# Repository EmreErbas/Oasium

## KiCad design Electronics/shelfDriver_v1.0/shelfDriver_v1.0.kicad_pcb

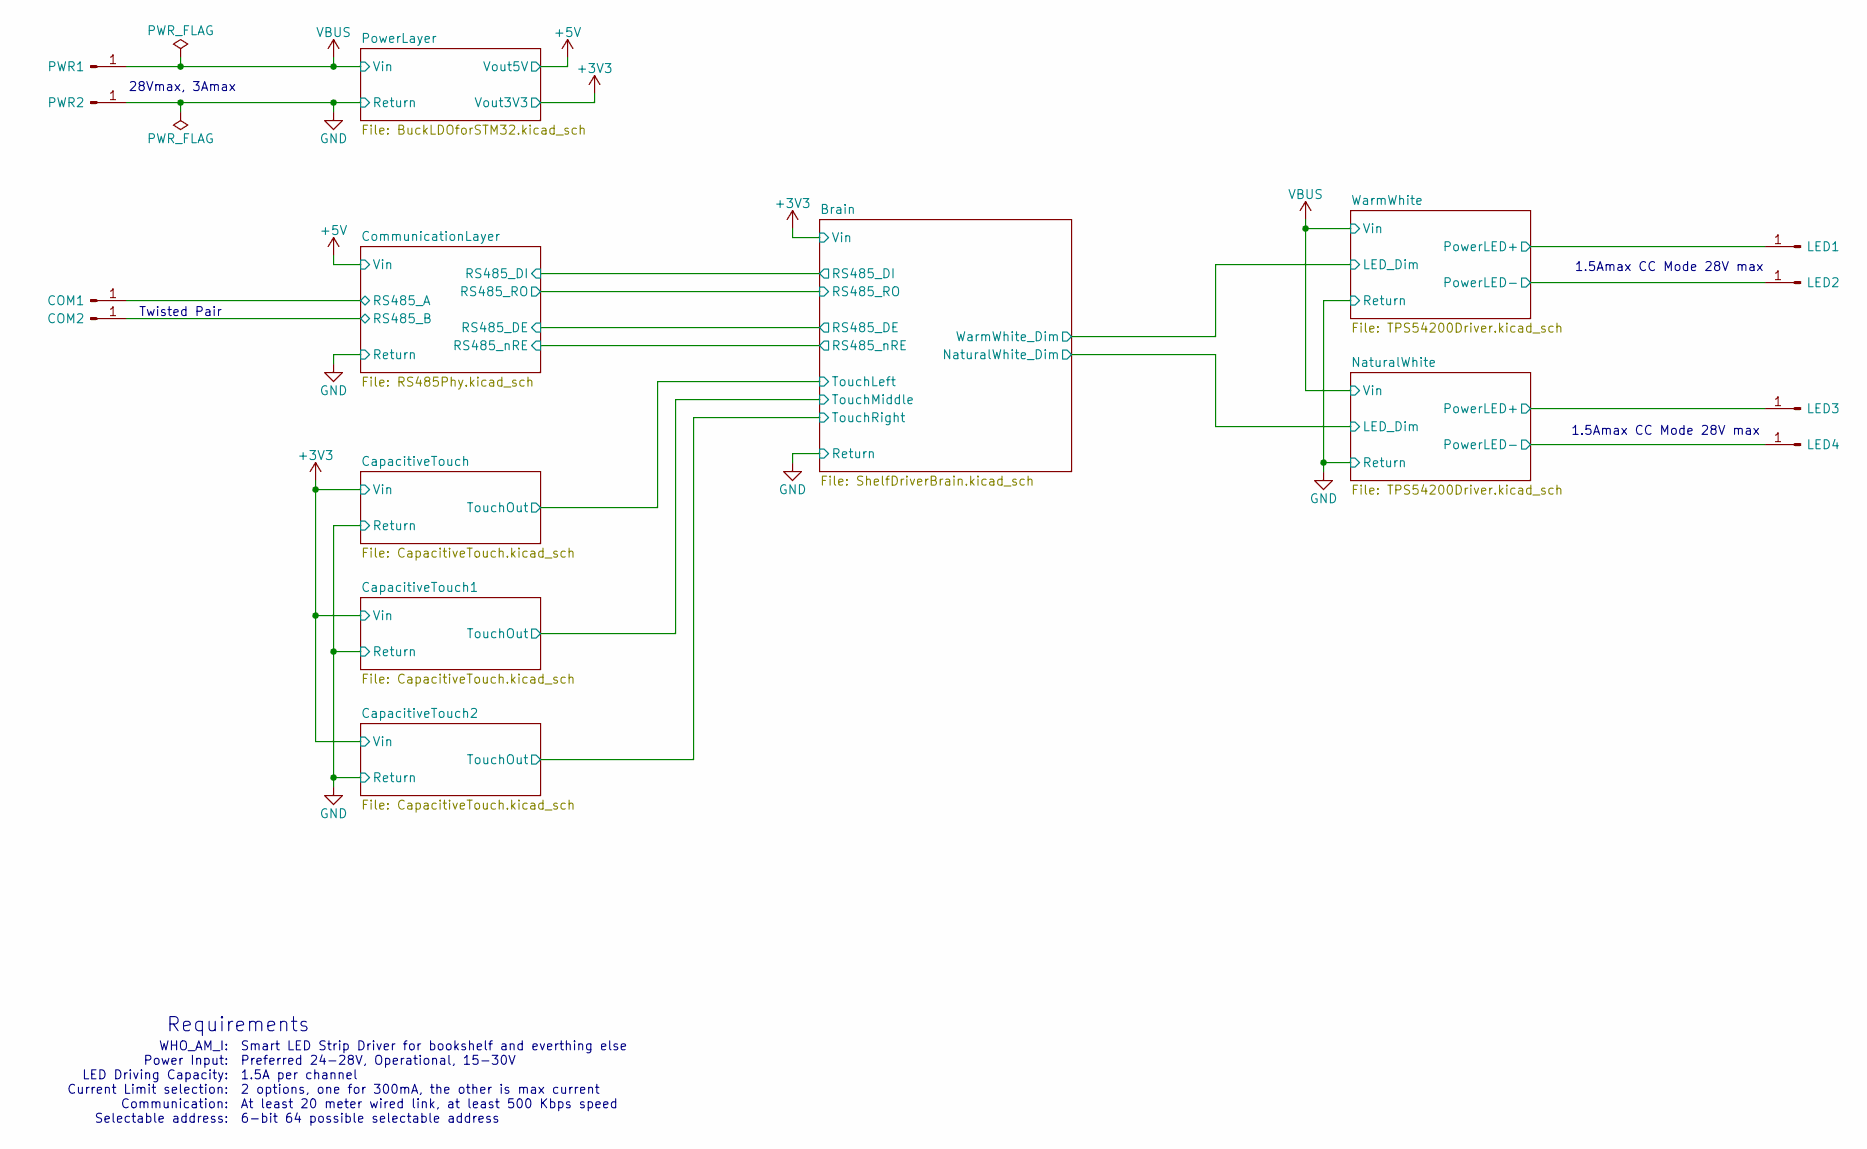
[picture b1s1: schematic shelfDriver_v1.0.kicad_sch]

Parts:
COM1, COM2: Conn_01x01_Pin; SolderPt_2.5x4mm
LED1, LED2, LED3, LED4: Conn_01x01_Pin; SolderPt_2.5x4mm
PWR1, PWR2: Conn_01x01_Pin; SolderPt_2.5x4mm

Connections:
/CommunicationLayer/RS485_A: COM1.1; also elsewhere on the board
/CommunicationLayer/RS485_B: COM2.1; also elsewhere on the board
/NaturalWhite/PowerLED+: LED3.1; also elsewhere on the board
/NaturalWhite/PowerLED-: LED4.1; also elsewhere on the board
/WarmWhite/PowerLED+: LED1.1; also elsewhere on the board
/WarmWhite/PowerLED-: LED2.1; also elsewhere on the board
GND: PWR2.1; also elsewhere on the board
VBUS: PWR1.1; also elsewhere on the board

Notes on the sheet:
Requirements
Smart LED Strip Driver for bookshelf and everthing else Preferred 24-28V, Operational, 15-30V 1.5A per channel 2 options, one for 300mA, the other is max current At least 20 meter wired link, at least 500 Kbps speed 6-bit 64 possible selectable address
1.5Amax CC Mode 28V max
28Vmax, 3Amax
Twisted Pair
WHO_AM_I: Power Input: LED Driving Capacity: Current Limit selection: Communication: Selectable address:

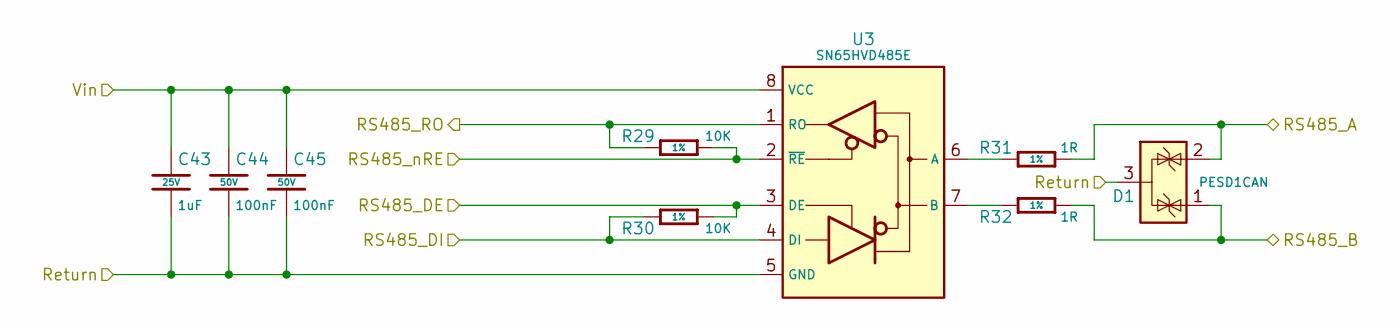
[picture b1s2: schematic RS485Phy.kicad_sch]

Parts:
C43: 1uF; C-0402; Voltage 25V; MFR. Part # CL05A105KA5NQNC; JLCPCB Part # C52923
C44, C45: 100nF; C-0402; Voltage 50V; MFR. Part # CL05B104KB54PNC; JLCPCB Part # C307331
D1: PESD1CAN; SOT-23; MFR. Part # PESD1CAN; JLCPCB Part # C343993
R29, R30: 10K; R-0402; Tolerance 1%; MFR. Part # 0402WGF1002TCE; JLCPCB Part # C25744
R31, R32: 1R; R-0402; Tolerance 1%; MFR. Part # 0402WGF100KTCE; JLCPCB Part # C25086
U3: SN65HVD485E; Texas_R-PDSO-G8; MFR.Part # SN65HVD485EDR; JLCPCB Part # C27899

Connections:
+5V: C43.1, C44.1, C45.1, U3.8 (VCC); also elsewhere on the board
/Brain/RS485_DE: R30.2, U3.3 (DE); also elsewhere on the board
/Brain/RS485_DI: R30.1, U3.4 (DI); also elsewhere on the board
/Brain/RS485_RO: R29.1, U3.1 (RO); also elsewhere on the board
/Brain/RS485_nRE: R29.2, U3.2 (~RE); also elsewhere on the board
/CommunicationLayer/RS485_A: D1.2 (K), R31.2; also elsewhere on the board
/CommunicationLayer/RS485_B: D1.1 (K), R32.2; also elsewhere on the board
GND: C43.2, C44.2, C45.2, D1.3 (A), U3.5 (GND); also elsewhere on the board
unnamed: R31.1, U3.6 (A)
unnamed: R32.1, U3.7 (B)

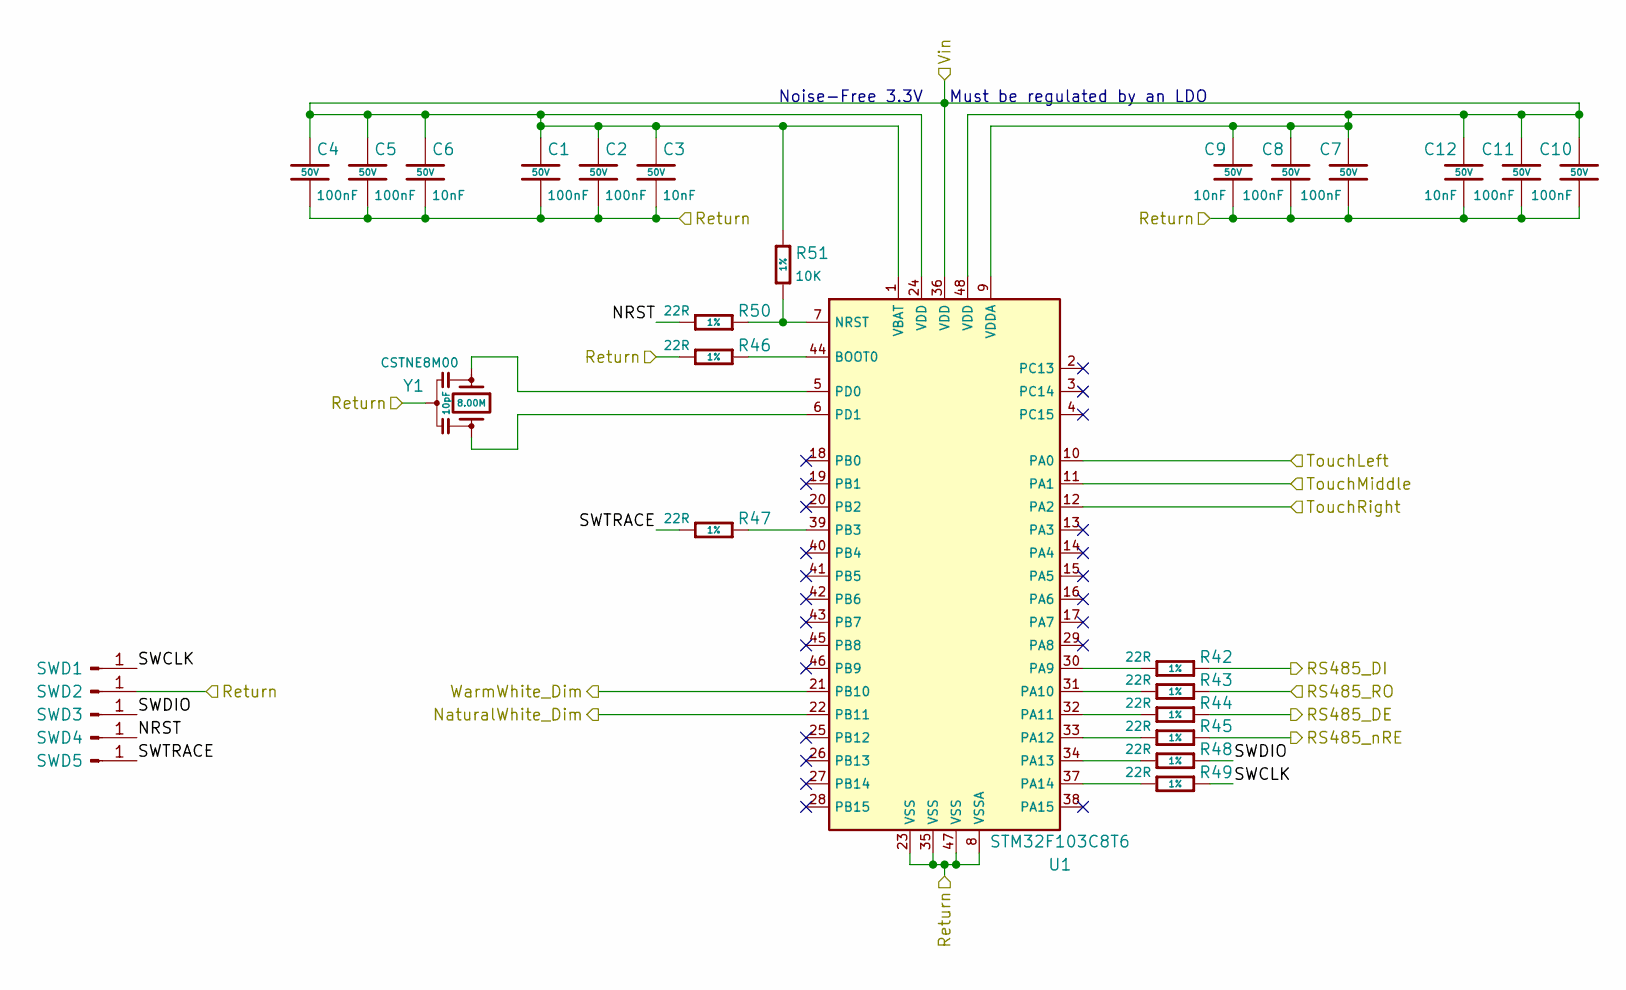
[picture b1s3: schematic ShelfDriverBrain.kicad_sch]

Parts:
C1, C2, C4, C5, C7, C8, C10, C11: 100nF; C-0402; Voltage 50V; MFR. Part # CL05B104KB54PNC; JLCPCB Part # C307331
C3, C6, C9, C12: 10nF; C-0402; Voltage 50V; MFR. Part # CL05B103KB5NNNC; JLCPCB Part # C15195
R42, R43, R44, R45, R46, R47, R48, R49, R50: 22R; R-0402; Tolerance 1%; MFR. Part # 0402WGF220JTCE; JLCPCB Part # C25092
R51: 10K; R-0402; Tolerance 1%; MFR. Part # 0402WGF1002TCE; JLCPCB Part # C25744
SWD1, SWD2, SWD3, SWD4, SWD5: Conn_01x01_Pin; SolderPt_1x1.5mm
U1: STM32F103C8T6; LQFP-48; MFR. Part # STM32F103C8T6; JLCPCB Part # C8734
Y1: CSTNE8M00; CSTNE; MFR. Part # CSTNE8M00G520000R0; JLCPCB Part # C907975

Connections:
+3V3: C1.1, C2.1, C3.1, C4.1, C5.1, C6.1, C7.1, C8.1, C9.1, C10.1, C11.1, C12.1, R51.1, U1.1 (VBAT), U1.9 (VDDA), U1.24 (VDD), U1.36 (VDD), U1.48 (VDD); also elsewhere on the board
/Brain/NRST: R50.2, SWD4.1
/Brain/NaturalWhite_Dim: U1.22 (PB11); also elsewhere on the board
/Brain/RS485_DE: R44.1; also elsewhere on the board
/Brain/RS485_DI: R42.1; also elsewhere on the board
/Brain/RS485_RO: R43.1; also elsewhere on the board
/Brain/RS485_nRE: R45.1; also elsewhere on the board
/Brain/SWCLK: R49.1, SWD1.1
/Brain/SWDIO: R48.1, SWD3.1
/Brain/SWTRACE: R47.2, SWD5.1
/Brain/TouchLeft: U1.10 (PA0); also elsewhere on the board
/Brain/TouchMiddle: U1.11 (PA1); also elsewhere on the board
/Brain/TouchRight: U1.12 (PA2); also elsewhere on the board
/Brain/WarmWhite_Dim: U1.21 (PB10); also elsewhere on the board
GND: C1.2, C2.2, C3.2, C4.2, C5.2, C6.2, C7.2, C8.2, C9.2, C10.2, C11.2, C12.2, R46.2, SWD2.1, U1.8 (VSSA), U1.23 (VSS), U1.35 (VSS), U1.47 (VSS), Y1.2; also elsewhere on the board
unnamed: R46.1, U1.44 (BOOT0)
unnamed: R50.1, R51.2, U1.7 (NRST)
unnamed: R42.2, U1.30 (PA9)
unnamed: R43.2, U1.31 (PA10)
unnamed: R44.2, U1.32 (PA11)
unnamed: R45.2, U1.33 (PA12)
unnamed: R48.2, U1.34 (PA13)
unnamed: R49.2, U1.37 (PA14)
unnamed: R47.1, U1.39 (PB3)
unnamed: U1.5 (PD0), Y1.1
unnamed: U1.6 (PD1), Y1.3

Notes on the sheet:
Noise-Free 3.3V Must be regulated by an LDO

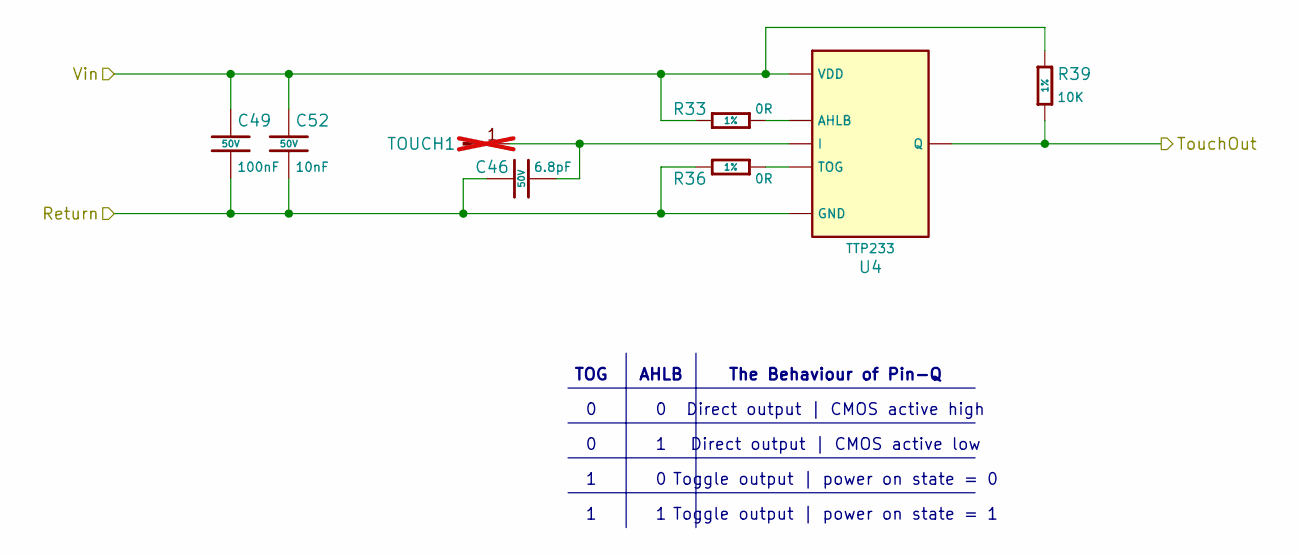
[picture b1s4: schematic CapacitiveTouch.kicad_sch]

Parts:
C46: 6.8pF; C-0402; Voltage 50V; MFR. Part # 0402CG6R8C500NT; JLCPCB Part # C1576
C49: 100nF; C-0402; Voltage 50V; MFR. Part # CL05B104KB54PNC; JLCPCB Part # C307331
C52: 10nF; C-0402; Voltage 50V; MFR. Part # CL05B103KB5NNNC; JLCPCB Part # C15195
R33, R36: 0R; R-0402; Tolerance 1%; MFR. Part # 0402WGF0000TCE; JLCPCB Part # C17168
R39: 10K; R-0402; Tolerance 1%; MFR. Part # 0402WGF1002TCE; JLCPCB Part # C25744
TOUCH1: Conn_01x01_Pin; SolderPt_2.5x4mm; not fitted
U4: TTP233; SOT-23-6; MFR. Part # TTP233H-BA6; JLCPCB Part # C2890349

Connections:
+3V3: C49.1, C52.1, R33.1, R39.1, U4.5 (VDD); also elsewhere on the board
/Brain/TouchLeft: R39.2, U4.1 (Q); also elsewhere on the board
GND: C46.1, C49.2, C52.2, R36.1, U4.2 (GND); also elsewhere on the board
unnamed: R33.2, U4.4 (AHLB)
unnamed: C46.2, U4.3 (I)
unnamed: R36.2, U4.6 (TOG)

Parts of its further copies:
C47, C48: 6.8pF; C-0402; Voltage 50V; MFR. Part # 0402CG6R8C500NT; JLCPCB Part # C1576
C50, C51: 100nF; C-0402; Voltage 50V; MFR. Part # CL05B104KB54PNC; JLCPCB Part # C307331
C53, C54: 10nF; C-0402; Voltage 50V; MFR. Part # CL05B103KB5NNNC; JLCPCB Part # C15195
R34, R35, R37, R38: 0R; R-0402; Tolerance 1%; MFR. Part # 0402WGF0000TCE; JLCPCB Part # C17168
R40, R41: 10K; R-0402; Tolerance 1%; MFR. Part # 0402WGF1002TCE; JLCPCB Part # C25744
U8, U9: TTP233; SOT-23-6; MFR. Part # TTP233H-BA6; JLCPCB Part # C2890349

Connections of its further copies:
+3V3: C50.1, C51.1, C53.1, C54.1, R34.1, R35.1, R40.1, R41.1, U8.5 (VDD), U9.5 (VDD); also elsewhere on the board
/Brain/TouchMiddle: R40.2, U8.1 (Q); also elsewhere on the board
/Brain/TouchRight: R41.2, U9.1 (Q); also elsewhere on the board
GND: C47.1, C48.1, C50.2, C51.2, C53.2, C54.2, R37.1, R38.1, U8.2 (GND), U9.2 (GND); also elsewhere on the board
unnamed: R34.2, U8.4 (AHLB)
unnamed: C47.2, U8.3 (I)
unnamed: R37.2, U8.6 (TOG)
unnamed: R35.2, U9.4 (AHLB)
unnamed: C48.2, U9.3 (I)
unnamed: R38.2, U9.6 (TOG)

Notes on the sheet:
Direct output | CMOS active high
Toggle output | power on state = 0
Direct output | CMOS active low
The Behaviour of Pin-Q
Toggle output | power on state = 1
TOG
AHLB

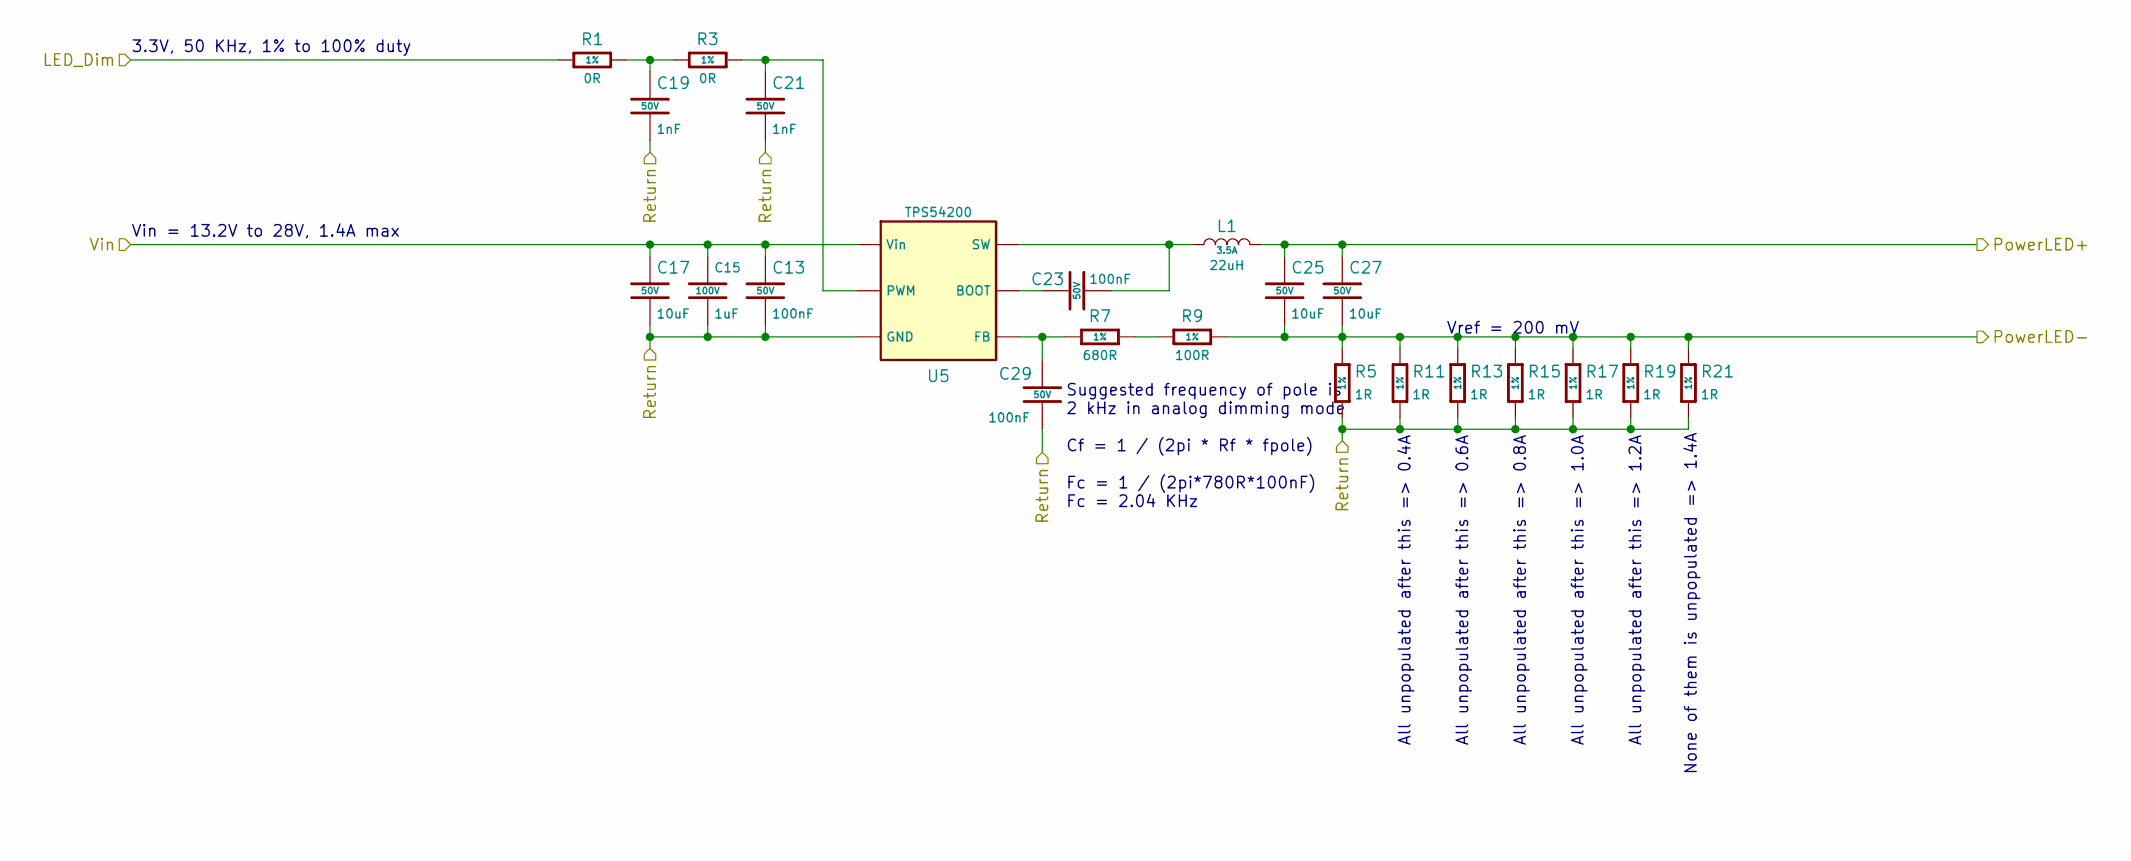
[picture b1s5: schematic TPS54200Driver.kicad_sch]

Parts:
C13, C23, C29: 100nF; C-0402; Voltage 50V; MFR. Part # CL05B104KB54PNC; JLCPCB Part # C307331
C15: 1uF; C-1206; Voltage 100V; MFR. Part # NC1206B105M101CEGN; JLCPCB Part # C2961023
C17, C25, C27: 10uF; C-0805; Voltage 50V; MFR. Part # GRM21BR61H106KE43L; JLCPCB Part # C440198
C19, C21: 1nF; C-0402; Voltage 50V; MFR. Part # 0402B102K500NT; JLCPCB Part # C1523
L1: 22uH; L-7.1-6.6; MFR. Part # SMMS0630-220M; JLCPCB Part # C128694
R1, R3: 0R; R-0402; Tolerance 1%; MFR. Part # 0402WGF0000TCE; JLCPCB Part # C17168
R5, R11, R13, R15, R17, R19, R21: 1R; R-0402; Tolerance 1%; MFR. Part # 0402WGF100KTCE; JLCPCB Part # C25086
R7: 680R; R-0402; Tolerance 1%; MFR. Part # 0402WGF6800TCE; JLCPCB Part # C25130
R9: 100R; R-0402; Tolerance 1%; MFR. Part # 0402WGF1000TCE; JLCPCB Part # C25076
U5: TPS54200; SOT-23-6; MFR. Part # TPS54200DDCR; JLCPCB Part # C177139

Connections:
/Brain/WarmWhite_Dim: R1.1; also elsewhere on the board
/WarmWhite/PowerLED+: C25.1, C27.1, L1.2; also elsewhere on the board
/WarmWhite/PowerLED-: C25.2, C27.2, R5.1, R9.2, R11.1, R13.1, R15.1, R17.1, R19.1, R21.1; also elsewhere on the board
GND: C13.2, C15.2, C17.2, C19.2, C21.2, C29.2, R5.2, R11.2, R13.2, R15.2, R17.2, R19.2, R21.2, U5.1 (GND); also elsewhere on the board
unnamed: C19.1, R1.2, R3.1
unnamed: R7.2, R9.1
unnamed: C23.1, U5.6 (BOOT)
unnamed: C29.1, R7.1, U5.4 (FB)
unnamed: C21.1, R3.2, U5.5 (PWM)
unnamed: C23.2, L1.1, U5.2 (SW)
VBUS: C13.1, C15.1, C17.1, U5.3 (Vin); also elsewhere on the board

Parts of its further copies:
C14, C24, C30: 100nF; C-0402; Voltage 50V; MFR. Part # CL05B104KB54PNC; JLCPCB Part # C307331
C16: 1uF; C-1206; Voltage 100V; MFR. Part # NC1206B105M101CEGN; JLCPCB Part # C2961023
C18, C26, C28: 10uF; C-0805; Voltage 50V; MFR. Part # GRM21BR61H106KE43L; JLCPCB Part # C440198
C20, C22: 1nF; C-0402; Voltage 50V; MFR. Part # 0402B102K500NT; JLCPCB Part # C1523
L2: 22uH; L-7.1-6.6; MFR. Part # SMMS0630-220M; JLCPCB Part # C128694
R2, R4: 0R; R-0402; Tolerance 1%; MFR. Part # 0402WGF0000TCE; JLCPCB Part # C17168
R6, R12, R14, R16, R18, R20, R22: 1R; R-0402; Tolerance 1%; MFR. Part # 0402WGF100KTCE; JLCPCB Part # C25086
R8: 680R; R-0402; Tolerance 1%; MFR. Part # 0402WGF6800TCE; JLCPCB Part # C25130
R10: 100R; R-0402; Tolerance 1%; MFR. Part # 0402WGF1000TCE; JLCPCB Part # C25076
U6: TPS54200; SOT-23-6; MFR. Part # TPS54200DDCR; JLCPCB Part # C177139

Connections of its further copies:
/Brain/NaturalWhite_Dim: R2.1; also elsewhere on the board
/NaturalWhite/PowerLED+: C26.1, C28.1, L2.2; also elsewhere on the board
/NaturalWhite/PowerLED-: C26.2, C28.2, R6.1, R10.2, R12.1, R14.1, R16.1, R18.1, R20.1, R22.1; also elsewhere on the board
GND: C14.2, C16.2, C18.2, C20.2, C22.2, C30.2, R6.2, R12.2, R14.2, R16.2, R18.2, R20.2, R22.2, U6.1 (GND); also elsewhere on the board
unnamed: C20.1, R2.2, R4.1
unnamed: R8.2, R10.1
unnamed: C24.1, U6.6 (BOOT)
unnamed: C30.1, R8.1, U6.4 (FB)
unnamed: C22.1, R4.2, U6.5 (PWM)
unnamed: C24.2, L2.1, U6.2 (SW)
VBUS: C14.1, C16.1, C18.1, U6.3 (Vin); also elsewhere on the board

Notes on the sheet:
None of them is unpopulated => 1.4A
Vin = 13.2V to 28V, 1.4A max
All unpopulated after this => 0.6A
All unpopulated after this => 1.2A
3.3V, 50 KHz, 1% to 100% duty
Vref = 200 mV
All unpopulated after this => 1.0A
All unpopulated after this => 0.4A
All unpopulated after this => 0.8A
Suggested frequency of pole is 2 kHz in analog dimming mode Cf = 1 / (2pi * Rf * fpole) Fc = 1 / (2pi*780R*100nF) Fc = 2.04 KHz

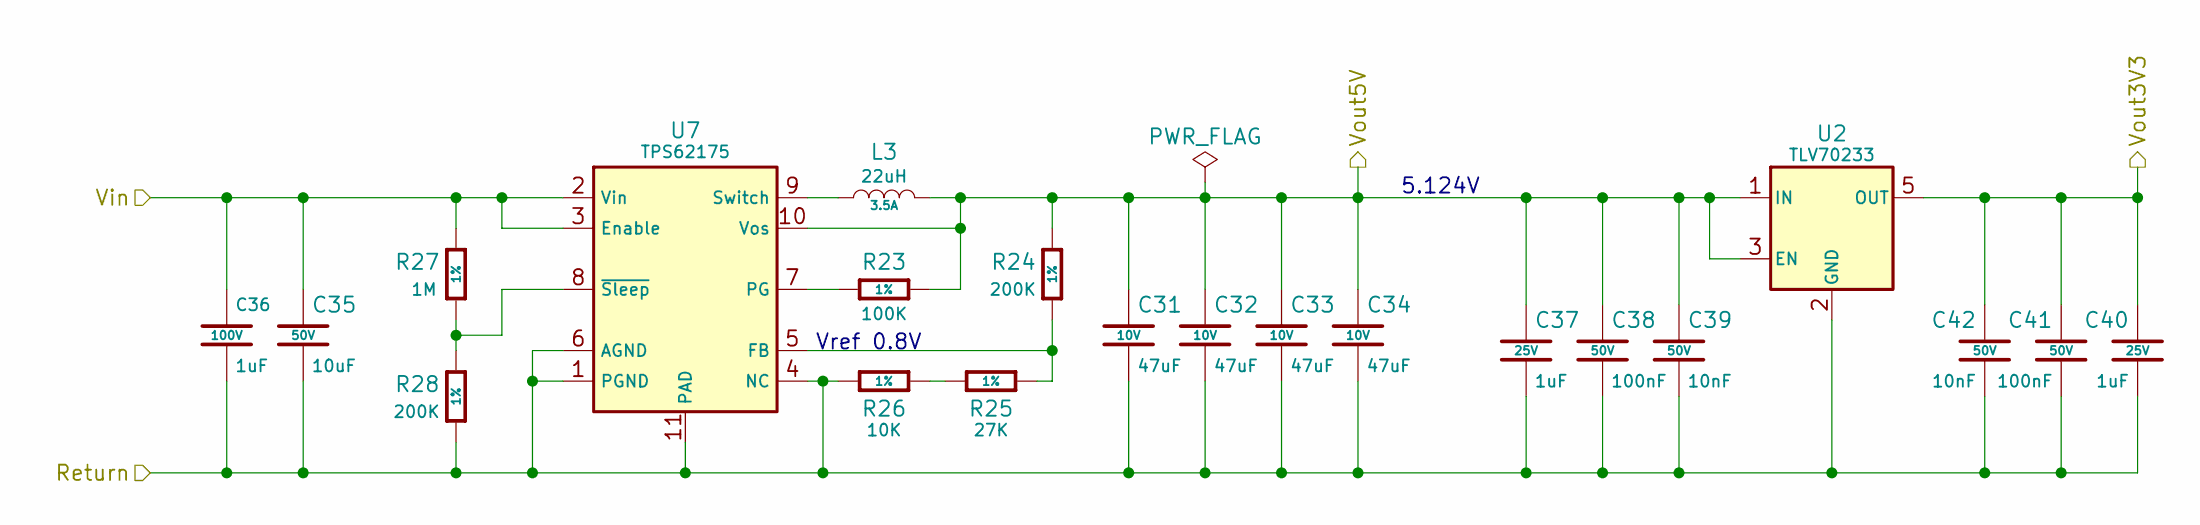
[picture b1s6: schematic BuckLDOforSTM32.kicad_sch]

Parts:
C31, C32, C33, C34: 47uF; C-1210; Voltage 10V; MFR. Part # C3225X5R1A476MT000E; JLCPCB Part # C76680
C35: 10uF; C-0805; Voltage 50V; MFR. Part # GRM21BR61H106KE43L; JLCPCB Part # C440198
C36: 1uF; C-1206; Voltage 100V; MFR. Part # NC1206B105M101CEGN; JLCPCB Part # C2961023
C37, C40: 1uF; C-0402; Voltage 25V; MFR. Part # CL05A105KA5NQNC; JLCPCB Part # C52923
C38, C41: 100nF; C-0402; Voltage 50V; MFR. Part # CL05B104KB54PNC; JLCPCB Part # C307331
C39, C42: 10nF; C-0402; Voltage 50V; MFR. Part # CL05B103KB5NNNC; JLCPCB Part # C15195
L3: 22uH; L-7.1-6.6; MFR. Part # SMMS0630-220M; JLCPCB Part # C128694
R23: 100K; R-0402; Tolerance 1%; MFR. Part # 0402WGF1003TCE; JLCPCB Part # C25741
R24, R28: 200K; R-0402; Tolerance 1%; MFR. Part # 0402WGF2003TCE; JLCPCB Part # C25764
R25: 27K; R-0402; Tolerance 1%; MFR. Part # 0402WGF2702TCE; JLCPCB Part # C25771
R26: 10K; R-0402; Tolerance 1%; MFR. Part # 0402WGF1002TCE; JLCPCB Part # C25744
R27: 1M; R-0402; Tolerance 1%; MFR. Part # 0402WGF1004TCE; JLCPCB Part # C26083
U2: TLV70233; SOT-23-5; MFR.Part # TLV70233DBVR; JLCPCB Part # C26833
U7: TPS62175; WSON10-2x3; MFR.Part # TPS62175DQCR; JLCPCB Part # C32097

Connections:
+3V3: C40.1, C41.1, C42.1, U2.5 (OUT); also elsewhere on the board
+5V: C31.1, C32.1, C33.1, C34.1, C37.1, C38.1, C39.1, L3.2, R23.2, R24.1, U2.1 (IN), U2.3 (EN), U7.10 (Vos); also elsewhere on the board
GND: C31.2, C32.2, C33.2, C34.2, C35.2, C36.2, C37.2, C38.2, C39.2, C40.2, C41.2, C42.2, R26.2, R28.2, U2.2 (GND), U7.1 (PGND), U7.4 (NC), U7.6 (AGND), U7.11 (PAD); also elsewhere on the board
unnamed: R25.2, R26.1
unnamed: R24.2, R25.1, U7.5 (FB)
unnamed: R23.1, U7.7 (PG)
unnamed: L3.1, U7.9 (Switch)
unnamed: R27.2, R28.1, U7.8 (~Sleep)
VBUS: C35.1, C36.1, R27.1, U7.2 (Vin), U7.3 (Enable); also elsewhere on the board

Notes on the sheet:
Vref 0.8V
5.124V

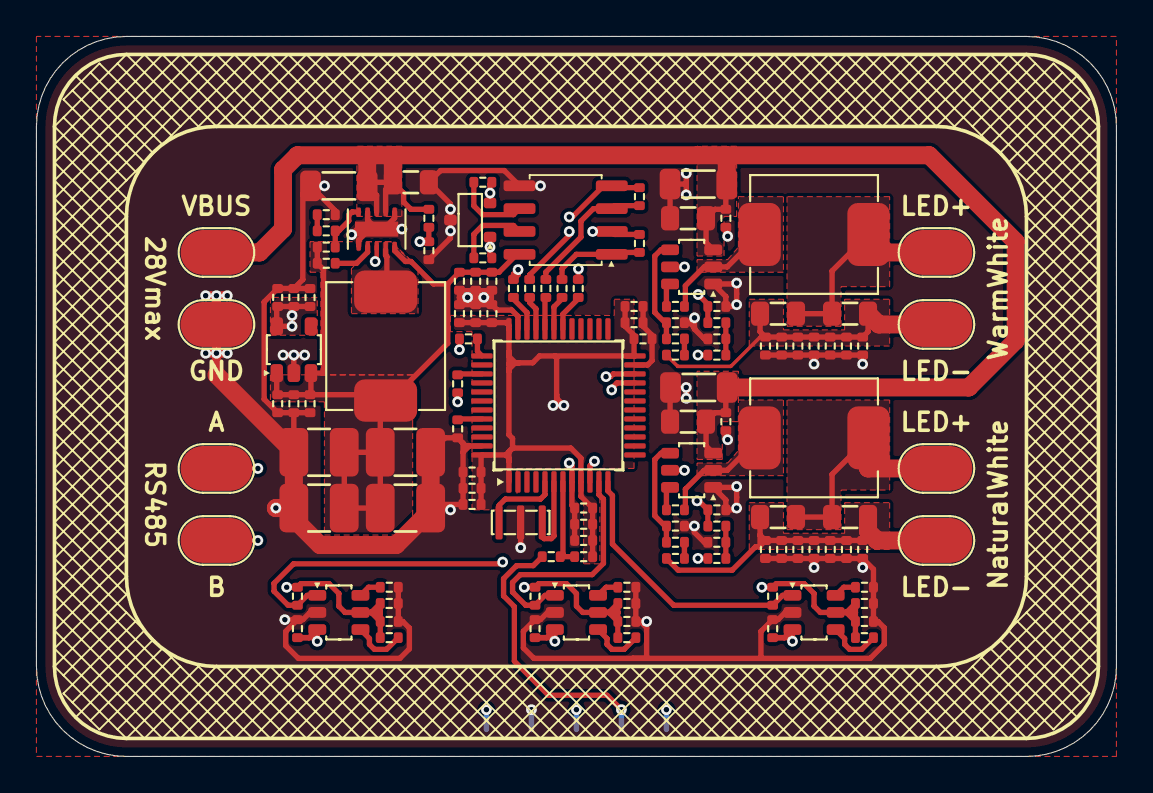
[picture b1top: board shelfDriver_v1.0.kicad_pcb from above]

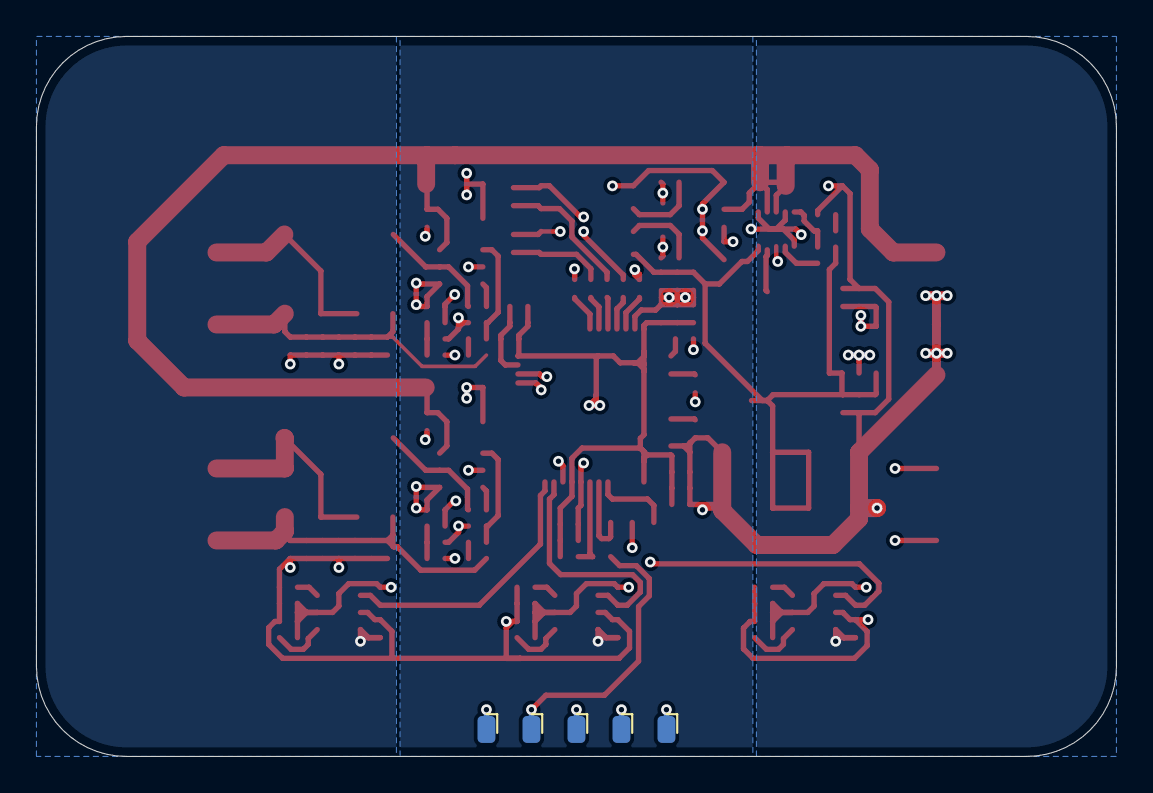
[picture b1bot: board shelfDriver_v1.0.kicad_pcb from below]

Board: 4 copper layers, 60.0 x 40.0 mm, 132 parts (5 on the bottom side), 62 nets.

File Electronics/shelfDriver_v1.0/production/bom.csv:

Designator,Footprint,Quantity,Value,LCSC Part #
"C1, C10, C11, C13, C14, C2, C23, C24, C29, C30, C38, C4, C41, C44, C45, C49, C5, C50, C51, C7, C8",C-0402,21,100nF,C307331
"C12, C3, C39, C42, C52, C53, C54, C6, C9",C-0402,9,10nF,C15195
"C15, C16, C36",C-1206,3,1uF,C2961023
"C17, C18, C25, C26, C27, C28, C35",C-0805,7,10uF,C440198
"C19, C20, C21, C22",C-0402,4,1nF,C1523
"C31, C32, C33, C34",C-1210,4,47uF,C76680
"C37, C40, C43",C-0402,3,1uF,C52923
"C46, C47, C48",C-0402,3,6.8pF,C1576
D1,SOT-23,1,PESD1CAN,C343993
"L1, L2, L3",L-7.1-6.6,3,22uH,C128694
"R1, R2, R3, R33, R34, R35, R36, R37, R38, R4",R-0402,10,0R,C17168
"R10, R9",R-0402,2,100R,C25076
"R11, R12, R13, R14, R15, R16, R17, R18, R19, R20, R21, R22, R31, R32, R5, R6",R-0402,16,1R,C25086
R23,R-0402,1,100K,C25741
"R24, R28",R-0402,2,200K,C25764
R25,R-0402,1,27K,C25771
"R26, R29, R30, R39, R40, R41, R51",R-0402,7,10K,C25744
R27,R-0402,1,1M,C26083
"R42, R43, R44, R45, R46, R47, R48, R49, R50",R-0402,9,22R,C25092
"R7, R8",R-0402,2,680R,C25130
U1,LQFP-48,1,STM32F103C8T6,C8734
U2,SOT-23-5,1,TLV70233,C26833
U3,Texas_R-PDSO-G8,1,SN65HVD485E,C27899
"U4, U8, U9",SOT-23-6,3,TTP233,C2890349
"U5, U6",SOT-23-6,2,TPS54200,C177139
U7,WSON10-2x3,1,TPS62175,C32097
Y1,CSTNE,1,CSTNE8M00,C907975

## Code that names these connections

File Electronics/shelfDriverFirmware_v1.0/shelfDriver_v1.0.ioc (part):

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Mcu.Name=STM32F103C(8-B)Tx
Mcu.Package=LQFP48
Mcu.UserName=STM32F103C8Tx
PA0-WKUP.GPIOParameters=GPIO_Label
PA0-WKUP.GPIO_Label=TouchLeft
PA0-WKUP.Signal=GPIO_Input
PA1.GPIOParameters=GPIO_Label
PA1.GPIO_Label=TouchMiddle
PA1.Signal=GPIO_Input
PA10.Mode=Asynchronous
PA10.Signal=USART1_RX
PA11.GPIOParameters=GPIO_Label
PA11.GPIO_Label=RS485_DE
PA11.Signal=GPIO_Output
PA12.GPIOParameters=GPIO_Label
PA12.GPIO_Label=RS485_nRE
PA12.Signal=GPIO_Output
PA13.Mode=Trace_Asynchronous_SW
PA13.Signal=SYS_JTMS-SWDIO
PA14.Mode=Trace_Asynchronous_SW
PA14.Signal=SYS_JTCK-SWCLK
PA2.GPIOParameters=GPIO_Label
PA2.GPIO_Label=TouchRight
PA2.Signal=GPIO_Input
PA9.Mode=Asynchronous
PA9.Signal=USART1_TX
PB10.GPIOParameters=GPIO_Speed,GPIO_Label
PB10.GPIO_Label=WarmWhite_Dim
PB10.GPIO_Speed=GPIO_SPEED_FREQ_HIGH
PB10.Signal=S_TIM2_CH3
PB11.GPIOParameters=GPIO_Speed,GPIO_Label
PB11.GPIO_Label=NaturalWhite_Dim
PB11.GPIO_Speed=GPIO_SPEED_FREQ_HIGH
PB11.Signal=S_TIM2_CH4
PB3.Mode=Trace_Asynchronous_SW
PB3.Signal=SYS_JTDO-TRACESWO
PD0-OSC_IN.Mode=HSE-External-Oscillator
PD0-OSC_IN.Signal=RCC_OSC_IN
PD1-OSC_OUT.Mode=HSE-External-Oscillator
PD1-OSC_OUT.Signal=RCC_OSC_OUT
RCC.SYSCLKFreq_VALUE=72000000
RCC.SYSCLKSource=RCC_SYSCLKSOURCE_PLLCLK
board=custom

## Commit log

2024-03-20 added shelf driver
2024-03-20 added submodules to the shelf driver
2024-12-03 complete
